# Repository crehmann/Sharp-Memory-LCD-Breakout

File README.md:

# Breakout Board for Sharp Memory Display (LS011B7DH03)

## Bill of Material

| Name                | Qty  | Package | Value                                        | Description                                                  |
| ------------------- | ---- | ------- | -------------------------------------------- | ------------------------------------------------------------ |
| FB1, FB2            | 2    | 0805    | 300mΩ DC Resistance, 600Ω impedance @ 100MHz | Ferrite Bead                                                 |
| C1                  | 1    | 0603    | 560pF/680pF                                  | Capacitor                                                    |
| C2, C3              | 2    | 0603    | 1uF                                          | Capacitor                                                    |
| R1/R2               | 1    | 0603    | 10kΩ                                         | Use either R1 **or** R2. Use R2 when VCOM toggling via EXTCOMIN pin (EIN) is used. |
| J3                  | 1    | SMD     | FH12-10S-0.5SH                               | FPC connector with 10 pins and 0.5mm pitch                   |
| LS011B7DH03 Display | 1    | -       |                                              | https://aliexpress.com/item/1005001809102193.html            |

See the BOM csv file in the [release zip-file](https://github.com/crehmann/Sharp-Memory-LCD-Breakout/releases) for LCSC part numbers 

**Note:** The current revision v0.3 is **not** tested. v0.2 was using wrong capacitor values but the schematic worked otherwise ([see picture](https://raw.githubusercontent.com/crehmann/Sharp-Memory-LCD-Breakout/main/Pictures/displayOnBreakoutBoard.png)).

**Assembly**: Soldering by hand is doable. The pads for the components are larger for easier soldering. However, for the FPC connecter good equipment and routine is required as it has a pitch of only 0.5mm

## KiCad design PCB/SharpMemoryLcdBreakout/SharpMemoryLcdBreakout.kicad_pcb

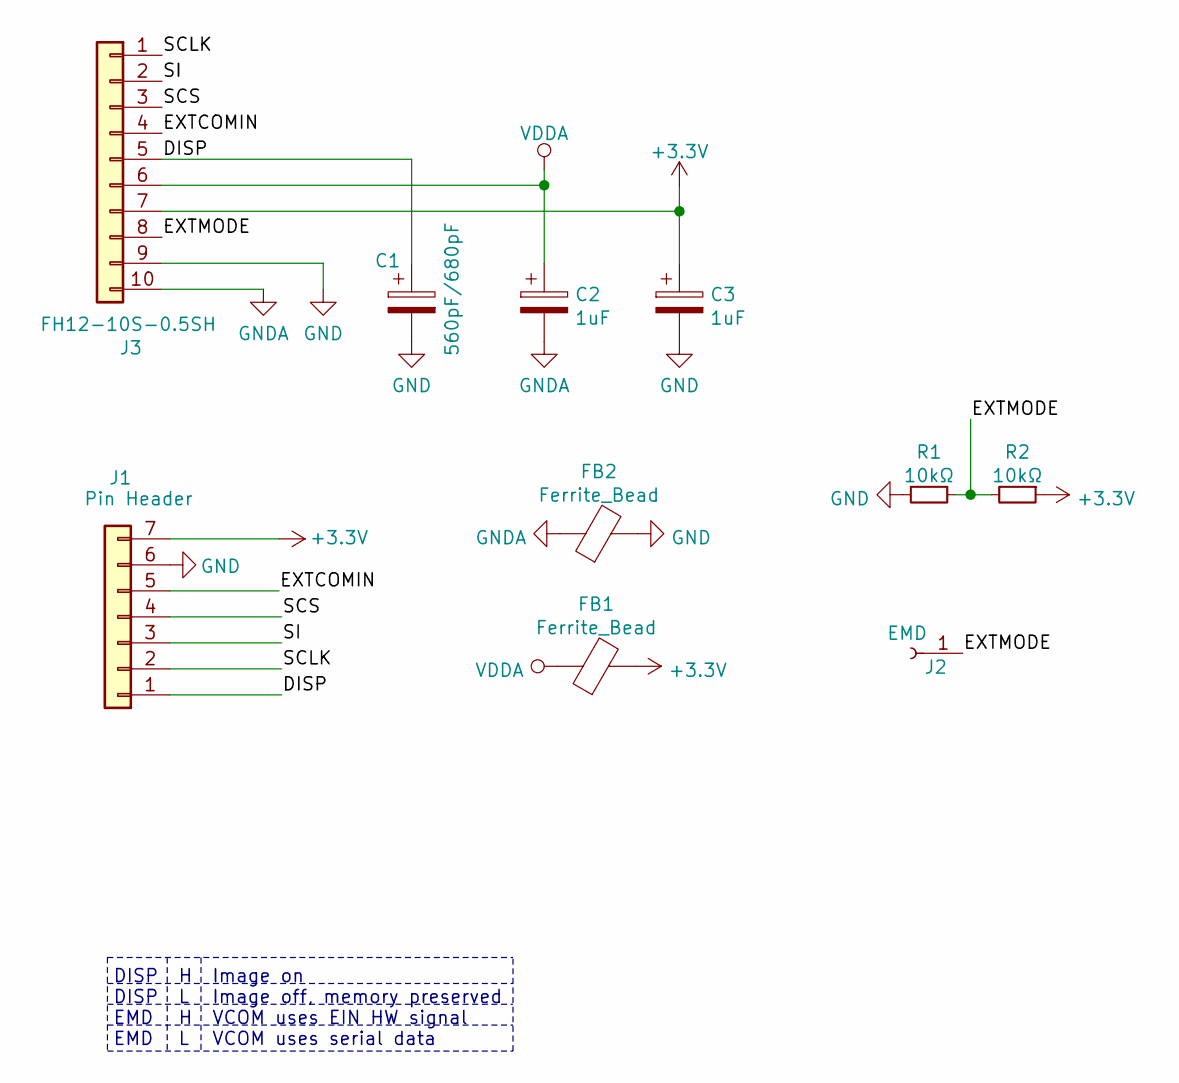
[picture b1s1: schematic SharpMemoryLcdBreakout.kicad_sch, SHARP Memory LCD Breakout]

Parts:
C1: 560pF/680pF; C_0603_1608Metric_Pad1.05x0.95mm_HandSolder; LCSC C1630
C2, C3: 1uF; C_0603_1608Metric_Pad1.05x0.95mm_HandSolder; LCSC C15849
FB1, FB2: Ferrite_Bead; R_0805_2012Metric_Pad1.15x1.40mm_HandSolder; LCSC C1017
J1: Pin Header; PinSocket_2Row_5+3_P2.54mm_Vertical
J2: EMD; TestPoint_Pad_D1.5mm
J3: FH12-10S-0.5SH; Hirose_FH12-10S-0.5SH_1x10-1MP_P0.50mm_Horizontal; LCSC C506791
R1, R2: 10kΩ; R_0603_1608Metric_Pad1.05x0.95mm_HandSolder; LCSC C25804

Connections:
+3V3: C3.1, FB1.2, J1.7, J3.7, R2.1
/DISP: C1.1, J1.1, J3.5
/EXTCOMIN: J1.5, J3.4
/EXTMODE: J2.1, J3.8, R1.1, R2.2
/SCLK: J1.2, J3.1
/SCS: J1.4, J3.3
/SI: J1.3, J3.2
GND: C1.2, C3.2, FB2.2, J1.6, J3.9, R1.2
GNDA: C2.2, FB2.1, J3.10
VDDA: C2.1, FB1.1, J3.6

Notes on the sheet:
DISP DISP EMD EMD
H L H L
Image on Image off, memory preserved VCOM uses EIN HW signal VCOM uses serial data

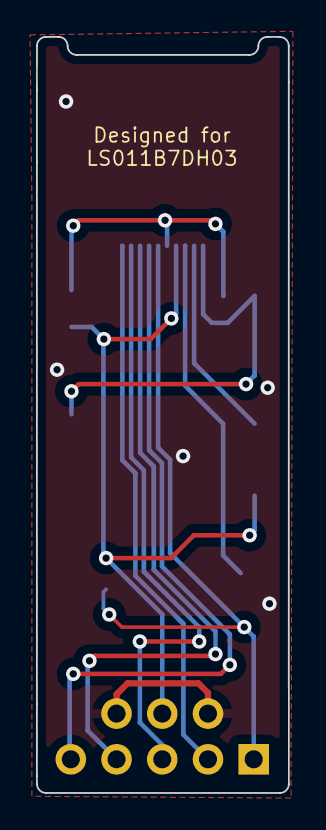
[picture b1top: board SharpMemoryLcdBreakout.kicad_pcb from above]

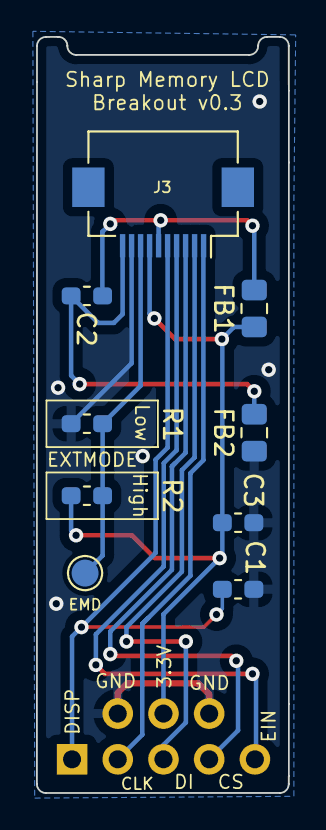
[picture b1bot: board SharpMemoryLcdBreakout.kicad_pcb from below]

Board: 2 copper layers, 14.0 x 42.0 mm, 10 parts (9 on the bottom side), 10 nets.

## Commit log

2021-10-20 Added project file with schematic and pcb design
2021-10-20 added mouse bite footprint
2021-10-20 increased size of pcb for smt assembly
2021-10-31 added pins for disp and emd
2021-11-06 switched EIN and EMD pin connections
2021-11-13 Mirrored FPC pins
2021-11-13 added panelized version
2021-12-01 increased part size (0805) and improved silk screen and added ferrite beads
2021-12-01 added rendered picture
2021-12-01 Add Readme and license
2021-12-03 added link
2021-12-04 Added BOM to readme and updated LCSC parts
2021-12-04 add link to releases
2021-12-04 added picture of working sample
2021-12-04 added link to picture
2021-12-04 going back to 0603 for easier part selection
2021-12-04 updated render image
